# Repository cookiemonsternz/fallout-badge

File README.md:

# Fallout Badge - SYNTH

Woah! A badge :O

## What is it?!

A badge with holes for mounting to a lanyard, containing within a full miniature analogue synthesizer / sequencer. 
This badge has a sawtooth vco core, with mcu controlled pitch and a manually controlled filter (modelled off of the Big Muff PI tone stage).

It also includes a small interface for playing and step recording a note sequence.

## Limitations

Due to the form factor / component limitations, this synth isn't fully featured, namely:
- It lacks a VCA (When its on it will constantly make noise)
- Untunable / no temperature compensation (Notes will be in tune with each other, but you'll only be able to tune it via software)
- Probably quite noisy and bad sounding - buzzers suck
  
## Screenshots

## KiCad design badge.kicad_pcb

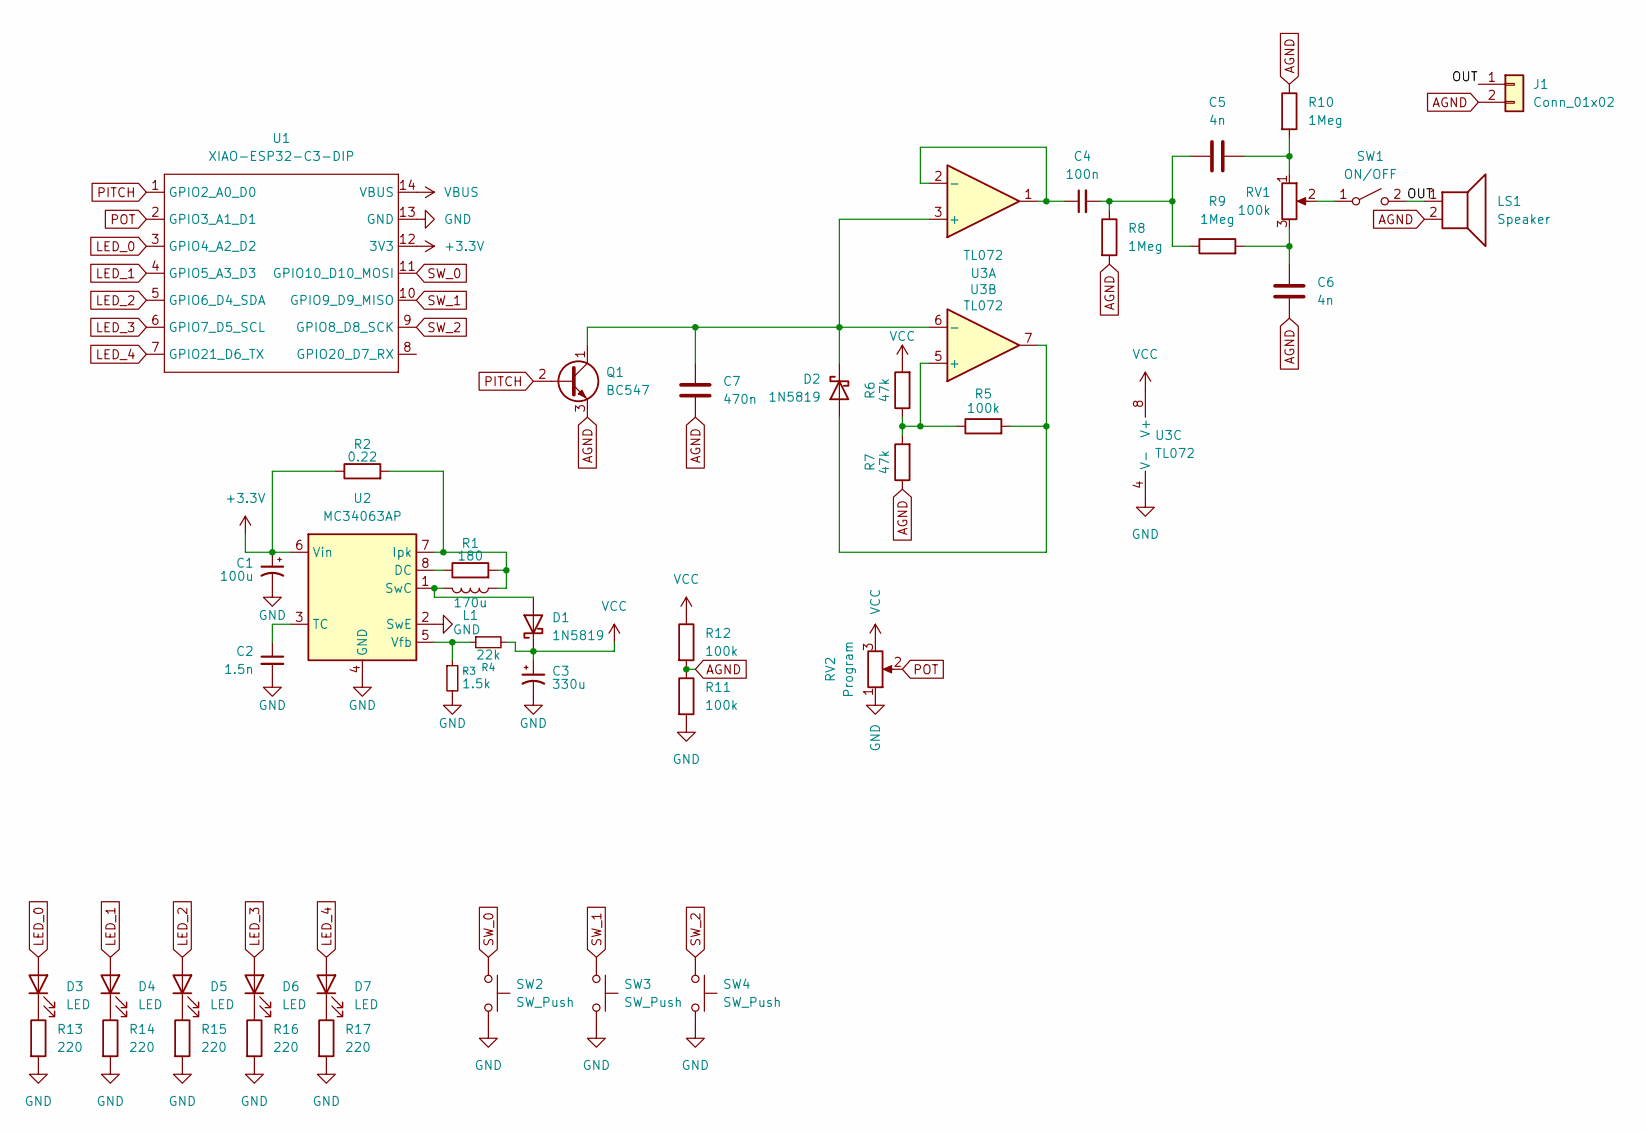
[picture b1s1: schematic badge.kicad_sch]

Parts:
C1: 100u; CP_Radial_D8.0mm_P3.50mm
C2: 1.5n; C_Disc_D4.3mm_W1.9mm_P5.00mm
C3: 330u; CP_Radial_D8.0mm_P3.50mm
C4: 100n; C_Disc_D4.3mm_W1.9mm_P5.00mm
C5, C6: 4n; C_Disc_D4.3mm_W1.9mm_P5.00mm
C7: 470n; C_Disc_D4.3mm_W1.9mm_P5.00mm
D1, D2: 1N5819; D_DO-41_SOD81_P10.16mm_Horizontal
D3, D4, D5, D6, D7: LED; LED_D5.0mm
J1: Conn_01x02; PinHeader_1x02_P2.54mm_Vertical
L1: 170u; L_Axial_L5.3mm_D2.2mm_P7.62mm_Horizontal_Vishay_IM-1
LS1: Speaker; Speaker-4mm
Q1: BC547; TO-92_Inline
R1: 180; R_Axial_DIN0204_L3.6mm_D1.6mm_P7.62mm_Horizontal
R2: 0.22; R_Axial_DIN0204_L3.6mm_D1.6mm_P7.62mm_Horizontal
R3: 1.5k; R_Axial_DIN0204_L3.6mm_D1.6mm_P7.62mm_Horizontal
R4: 22k; R_Axial_DIN0204_L3.6mm_D1.6mm_P7.62mm_Horizontal
R5, R11, R12: 100k; R_Axial_DIN0204_L3.6mm_D1.6mm_P7.62mm_Horizontal
R6, R7: 47k; R_Axial_DIN0204_L3.6mm_D1.6mm_P7.62mm_Horizontal
R8, R9, R10: 1Meg; R_Axial_DIN0204_L3.6mm_D1.6mm_P7.62mm_Horizontal
R13, R14, R15, R16, R17: 220; R_Axial_DIN0204_L3.6mm_D1.6mm_P7.62mm_Horizontal
RV1: 100k; Potentiometer_Alps_RK09K_Single_Vertical
RV2: Program; Potentiometer_Alps_RK09K_Single_Vertical
SW1: ON/OFF; PinSocket_1x02_P2.54mm_Vertical
SW2, SW3, SW4: SW_Push; SW_PUSH_6mm
U1: XIAO-ESP32-C3-DIP; XIAO-ESP32-C3-DIP-SMD
U2: MC34063AP; DIP-8_W7.62mm
U3: TL072; DIP-8_W7.62mm

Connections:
+3.3V: C1.1, R2.1, U1.12 (3V3), U2.6 (Vin)
/OUT: J1.1, LS1.1, SW1.2 (B); also elsewhere on the board
AGND: C6.1, C7.2, J1.2, LS1.2, Q1.3 (E), R7.1, R8.2, R10.1, R11.1, R12.2; also elsewhere on the board
GND: C1.2, C2.2, C3.2, R3.2, R11.2, R13.2, R14.2, R15.2, R16.2, R17.2, RV2.1, SW2.2, SW3.2, SW4.2, U1.13 (GND), U2.2 (SwE), U2.4 (GND), U3.4 (V-)
LED_0: D3.2 (A), U1.3 (GPIO4_A2_D2)
LED_1: D4.2 (A), U1.4 (GPIO5_A3_D3)
LED_2: D5.2 (A), U1.5 (GPIO6_D4_SDA)
LED_3: D6.2 (A), U1.6 (GPIO7_D5_SCL)
LED_4: D7.2 (A), U1.7 (GPIO21_D6_TX)
unnamed: C4.2, C5.1, R8.1, R9.1
unnamed: C5.2, R10.2, RV1.1
unnamed: C6.2, R9.2, RV1.3
unnamed: D1.2 (A), L1.1, U2.1 (SwC)
unnamed: D2.2 (A), R5.2, U3.7
unnamed: C7.1, D2.1 (K), Q1.1 (C), U3.3 (+), U3.6 (-)
unnamed: D3.1 (K), R13.1
unnamed: D4.1 (K), R14.1
unnamed: D5.1 (K), R15.1
unnamed: D6.1 (K), R16.1
unnamed: D7.1 (K), R17.1
unnamed 20: RV1.2, SW1.1 (A); also elsewhere on the board
unnamed: R1.1, U2.8 (DC)
unnamed: L1.2, R1.2, R2.2, U2.7 (Ipk)
unnamed: C2.1, U2.3 (TC)
unnamed: R3.1, R4.1, U2.5 (Vfb)
unnamed: C4.1, U3.1, U3.2 (-)
unnamed: R5.1, R6.1, R7.2, U3.5 (+)
PITCH: Q1.2 (B), U1.1 (GPIO2_A0_D0)
POT: RV2.2, U1.2 (GPIO3_A1_D1)
SW_0: SW2.1, U1.11 (GPIO10_D10_MOSI)
SW_1: SW3.1, U1.10 (GPIO9_D9_MISO)
SW_2: SW4.1, U1.9 (GPIO8_D8_SCK)
VBUS: U1.14 (VBUS)
VCC: C3.1, D1.1 (K), R4.2, R6.2, R12.1, RV2.3, U3.8 (V+)

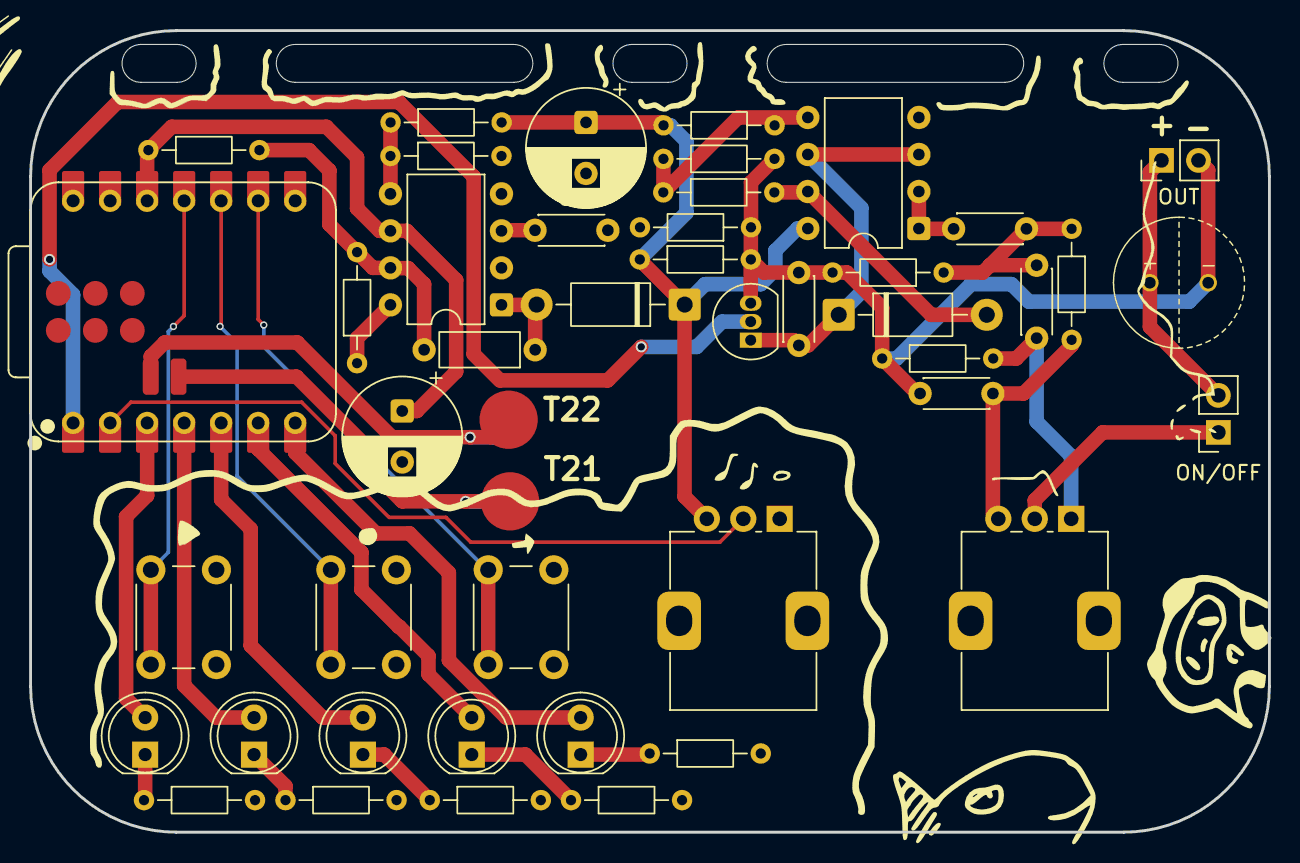
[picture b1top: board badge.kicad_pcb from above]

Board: 2 copper layers, 85.0 x 55.0 mm, 44 parts (0 on the bottom side), 33 nets.

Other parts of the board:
ON/OFF: ON/OFF; PinSocket_1x02_P2.54mm_Vertical
OUT: Conn_01x02; PinHeader_1x02_P2.54mm_Vertical

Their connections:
/OUT: ON/OFF.2 (B), OUT.1; also elsewhere on the board
AGND: OUT.2; also elsewhere on the board
unnamed 20: ON/OFF.1 (A); also elsewhere on the board
